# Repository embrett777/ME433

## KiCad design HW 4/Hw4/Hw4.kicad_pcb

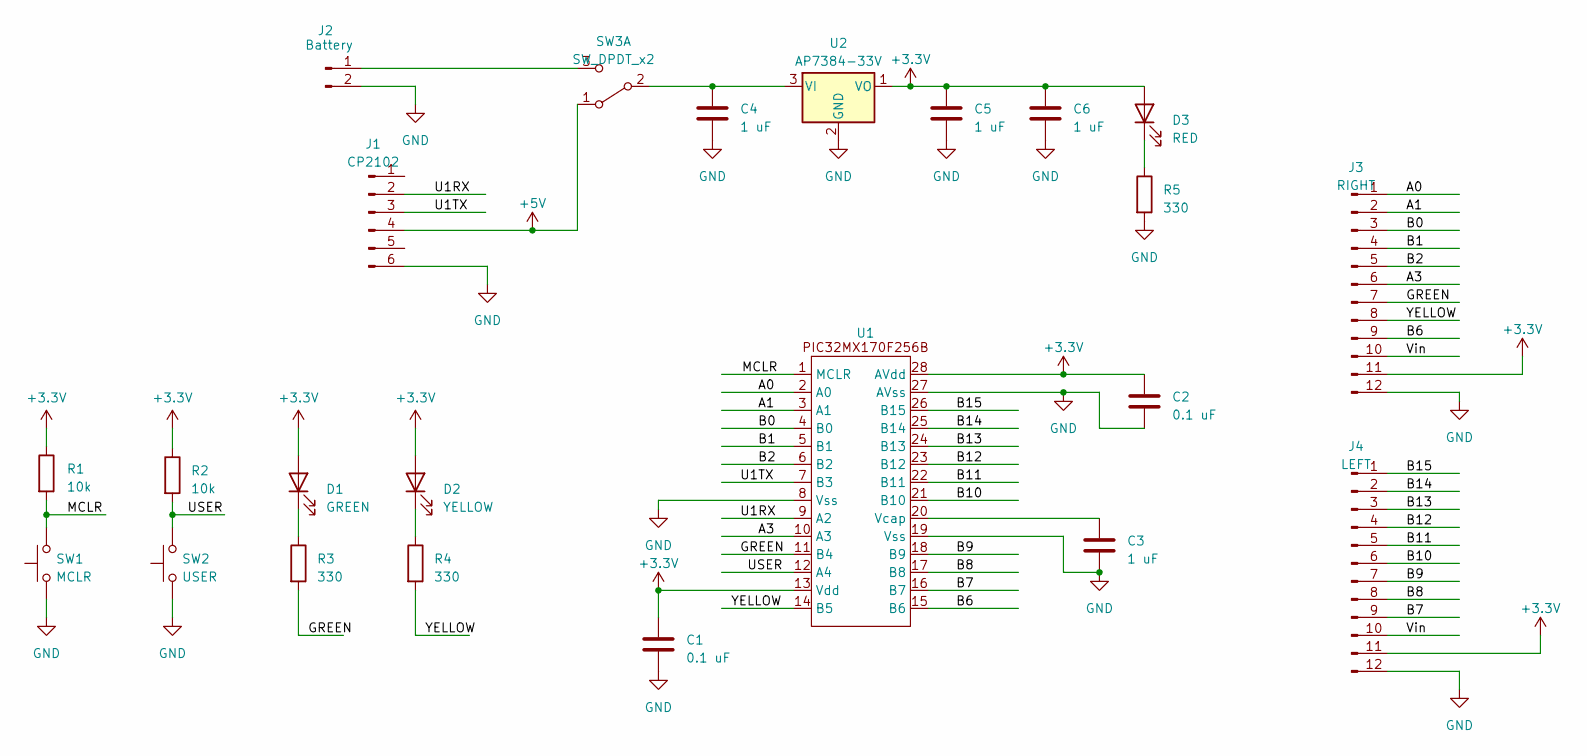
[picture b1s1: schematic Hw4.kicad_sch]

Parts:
C1, C2: 0.1 uF; C_Disc_D3.4mm_W2.1mm_P2.50mm
C3, C4, C5, C6: 1 uF; C_Disc_D5.1mm_W3.2mm_P5.00mm
D1: GREEN; LED_D3.0mm
D2: YELLOW; LED_D3.0mm
D3: RED; LED_D3.0mm
J1: CP2102; PinSocket_1x06_P2.54mm_Vertical
J2: Battery; PinSocket_1x02_P2.54mm_Vertical
J3: RIGHT; PinSocket_1x12_P2.54mm_Vertical
J4: LEFT; PinSocket_1x12_P2.54mm_Vertical
R1, R2: 10k; R_Axial_DIN0207_L6.3mm_D2.5mm_P7.62mm_Horizontal
R3, R4, R5: 330; R_Axial_DIN0207_L6.3mm_D2.5mm_P7.62mm_Horizontal
SW1: MCLR; pb
SW2: USER; pb
SW3: SW_DPDT_x2; slidesw2
U1: PIC32MX170F256B; DIP-28_W7.62mm_Socket
U2: AP7384-33V; TO-92L_Inline

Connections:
+3.3V: C1.1, C2.1, C5.1, C6.1, D1.2 (A), D2.2 (A), D3.2 (A), J3.11, J4.11, R1.1, R2.1, U1.13 (Vdd), U1.28 (AVdd), U2.1 (VO)
+5V: J1.4, SW3.1 (A)
/A0: J3.1, U1.2 (A0)
/A1: J3.2, U1.3 (A1)
/A3: J3.6, U1.10 (A3)
/B0: J3.3, U1.4 (B0)
/B1: J3.4, U1.5 (B1)
/B2: J3.5, U1.6 (B2)
/B6: J3.9, U1.15 (B6)
/B7: J4.9, U1.16 (B7)
/B8: J4.8, U1.17 (B8)
/B9: J4.7, U1.18 (B9)
/B10: J4.6, U1.21 (B10)
/B11: J4.5, U1.22 (B11)
/B12: J4.4, U1.23 (B12)
/B13: J4.3, U1.24 (B13)
/B14: J4.2, U1.25 (B14)
/B15: J4.1, U1.26 (B15)
/GREEN: J3.7, R3.2, U1.11 (B4)
/MCLR: R1.2, SW1.2, U1.1 (MCLR)
/U1RX: J1.2, U1.9 (A2)
/U1TX: J1.3, U1.7 (B3)
/USER: R2.2, SW2.2, U1.12 (A4)
/Vin: J3.10, J4.10
/YELLOW: J3.8, R4.2, U1.14 (B5)
GND: C1.2, C2.2, C3.2, C4.2, C5.2, C6.2, J1.6, J2.2, J3.12, J4.12, R5.2, SW1.1, SW2.1, U1.8 (Vss), U1.19 (Vss), U1.27 (AVss), U2.2 (GND)
unnamed: D1.1 (K), R3.1
unnamed: D2.1 (K), R4.1
unnamed: D3.1 (K), R5.1
unnamed: J2.1, SW3.3 (C)
unnamed: C4.1, SW3.2 (B), U2.3 (VI)
unnamed: C3.1, U1.20 (Vcap)

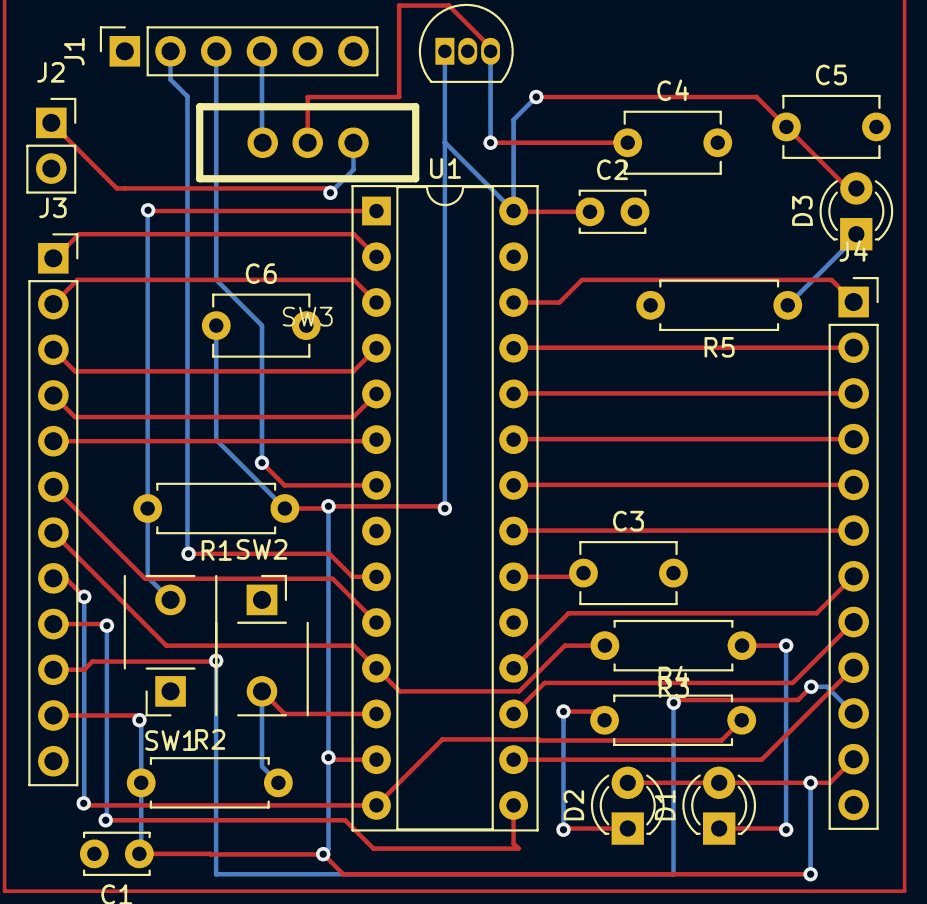
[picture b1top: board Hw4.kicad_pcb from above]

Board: 2 copper layers, 23 parts (0 on the bottom side), 32 nets.

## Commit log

2023-04-04 Creating homework 2
2023-04-04 Adding oscilloscope
2023-04-04 Other images
2023-04-04 Reorganizing folder
2023-04-09 Uploading hw 3 files
2023-04-27 PCB design
2023-04-27 Organizing
2023-04-27 Creating HW 5 docs
2023-04-29 Initializing pins
2023-04-29 Fixing CS pins
2023-04-29 Attempt 1
2023-04-29 Attempt 2
2023-04-30 Attempt 3
2023-04-30 Final code
2023-04-30 Adding screenshot
2023-05-03 Blinking gp7
2023-05-03 setting inputs and outputs
2023-05-03 read attempt 1
2023-05-03 read attempt 2
2023-05-03 Final code!
2023-05-03 creating homework 7 folder
2023-05-05 updating template
2023-05-13 moving plottter
2023-05-13 creating hw 8
2023-05-13 creating main code
2023-05-14 writing draw functions
2023-05-14 attempting to blink one pixel
2023-05-14 trying again
2023-05-14 functional blinking pixel
2023-05-14 functional counter display
2023-05-15 attempt 1 reading accelerometer
2023-05-15 practice files
2023-05-16 fixing fps
2023-05-17 MAF and IIR
2023-05-17 adding more images
2023-05-23 starting hw 10
2023-05-25 final working code
2023-05-30 homework 11
2023-06-02 servo homework
2023-06-08 HW 12
2023-06-08 creating website
2023-06-08 minor changes
2023-06-08 udpate
